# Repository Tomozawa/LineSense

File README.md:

# LineSense
NHK24用ラインセンサ基板。BOMは[こちら](https://docs.google.com/spreadsheets/d/12akROPWRgP_KYzk62EP3h0m6oYP8IBUy/edit?usp=sharing&ouid=100044542046978284478&rtpof=true&sd=true)

## バージョン履歴
### 初期版(2023/9/9)
初期バージョン。
### v1.1(2023/9/9)
センサが5V仕様だったので12Vから5Vに電源を変更。それに伴う回路定数変更。基板にシルク印刷のバージョン表記を追加。

## 概要
地面の色(水性塗料でペイントされている)を判別することができるセンサ。白かそれ以外(青、緑、オレンジ、黄、赤のいずれか)かを判別する。地面の下が白色である確率に応じた振幅の正弦波(10kHz)がSIG_OUTから出力される。出力された信号を包括線検波することで反射率を取得できる。LEDを10kHzで点滅させることで光の反射率をAM変調し、光学フィルタでLEDの波長以外をカットし、Q値の高いLCフィルタで10kHzの信号のみを抽出しているため、比較的地面と離れていても実用に耐えられるよう配慮している。これは、センサの位置を高めにすることでフィールドにある傾斜の影響を極力小さくするためである。

## 基板の作り方(推奨)
部品の温度特性を考慮して、未使用時でも3カ月に1回は校正を行うこと。また、実運用時には機械的な振動で半固定抵抗がずれるため、機体を起動させる際に攻勢を行うこと。

### 1. LED点灯回路を組む
Sheet 2/2 の部品、J1(EPコネクタ)、C7(電解コンデンサ)を取り付け、LEDが点灯することを確認する。また、TP1(テストポイント)から9~12kHzの矩形波が観測されるか確認する。

### 2. 受光回路を組む
Q1, R1, R10, C5を取り付け、白い紙に反射させたLED光に反応することを確認する(10kHz付近の波が確認できるはず)。出力波形はTP2(生信号)またはTP3(カップリング済み信号)で確認できる。信号が弱い場合はR10を時計回りに回すことでゲインを上げる。

### 3. プリアンプ/フィルタ/アンプを組む
残りの部品を取り付け、白い紙に反射させたLED光に反応することを確認する。出力波形はTP5またはコネクタから取ってくる。信号が弱い場合はR5を時計回りに回すことでプリアンプのゲインを上げる。

### 4. 光学フィルタをつける
光センサ(Q1)を20mm平方の青いセロハンで覆う。

### 5. 校正を行う
以下のセクションで説明のある方法で校正を行う。

## 校正の仕方
### LEDの点滅周波数の校正
TP1にオシロスコープのプローブを当て、R16を調整しながら10kHzの矩形波が出力されるようにする。R16を時計回りに回すと周波数が上がり、反時計回りに回すと周波数が下がる。

### 受光回路のゲインの校正
周囲を出来るだけ暗くし、センサを白い紙に水平に設置する。この時の紙との距離は、機体にセンサを搭載した時の高さに合わせる。R10を調整しながらTP3から100mVpp(0.1Vpp)の10kHzの矩形波が出力されるようにする。R10を時計回りに回すと波形が大きくなり、反時計回りに回すと波形が小さくなる。

### プリアンプのゲインの校正
受光回路のゲイン校正と同様の条件に加え、SIG_OUTに36Ωの負荷抵抗を接続した状態で、R5を調整しながらTP5で出てくる信号が歪まないギリギリまでゲインを上げる。TP5からは10kHz正弦波**のみ**が出力されるので、その頂点の部分(約3.0V~3.3V程度)が歪まない(つぶれない)限界までR5を時計回りに回す。

## 課題
### センサと地面の距離による影響が大きい
センサの出力が距離によって大きく変わるため、色の判断のためにはさまざまな波長の光の反射率を取得する必要がある。現状では青色(450nm)の反射率を見ているため、距離の変動による反射率の変化が検出できない

### プリアンプのカップリングコンデンサが機能しない
カップリングコンデンサの後ろを1MΩの抵抗でプルダウンすることでカップリングコンデンサに電流が流れ、カップリングの役割を果たす

### LEDが暗い
Q6のコレクタエミッタ管電圧が低く、負帰還がかかる前に電流が頭打ちになっている。R13を2.2kΩに下げることで90mA程度流れるようになる

### カップリングされているはずなのにプリアンプ出力にDC成分が乗る
原因は分からなかった。出力部分のRCローパスフィルタに原因があるかも。

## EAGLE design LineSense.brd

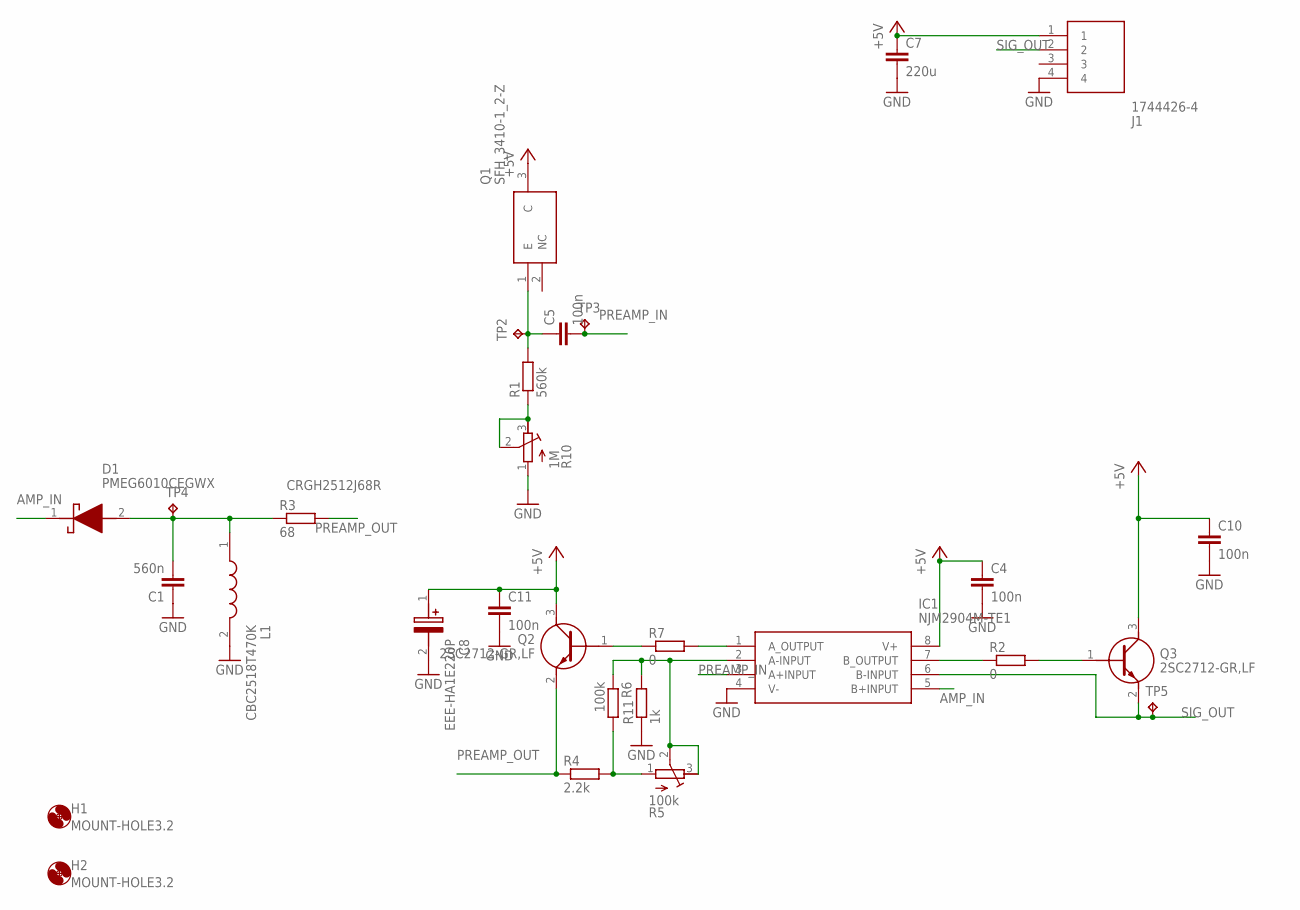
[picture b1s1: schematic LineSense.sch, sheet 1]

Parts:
C1: 560n; C0603
C4, C5, C10, C11: 100n; C0603
C7: 220u; C025-025X050
C8: EEE-HA1E220P; EEE1AA101SP
D1: PMEG6010CEGWX
H1, H2: MOUNT-HOLE3.2; 3,2
IC1: NJM2904M-TE1; SOP65P400X100-8N
J1: 1744426-4; 17444264
L1: CBC2518T470K; INDC2518X200N
Q1: SFH_3410-1_2-Z; SFH341012Z
Q2, Q3: 2SC2712-GR,LF; SSM3J334RLF
R1: 560k; R0603
R2, R7: 0; R0603
R3: 68; R2512
R4: 2.2k; R0603
R5: 100k; RTRIM3339P
R6: 100k; R0603
R10: 1M; RTRIM3339P
R11: 1k; R0603
TP2, TP3, TP4, TP5: TPB1,27; B1,27

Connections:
+5V: C4.1, C7.1, C8.1 (+), C10.1, C11.1, IC1.8 (V+), J1.1, Q1.3 (C), Q2.3 (C), Q3.3 (C); also elsewhere on the board
AMP_IN: D1.1 (K), IC1.5 (B+INPUT)
GND: C1.1, C4.2, C7.2, C8.2 (-), C10.2, C11.2, IC1.4 (V-), J1.4, L1.2, R10.1 (A), R11.1; also elsewhere on the board
unnamed: R1.1, R10.2 (S), R10.3 (E)
unnamed: IC1.1 (A_OUTPUT), R7.2
unnamed: Q2.1 (B), R7.1
unnamed: C5.1, Q1.1 (E), R1.2, TP2.TP
unnamed: R4.2, R5.1 (A), R6.2
unnamed: IC1.2 (A-INPUT), R5.2 (S), R5.3 (E), R6.1, R11.2
unnamed: IC1.7 (B_OUTPUT), R2.1
unnamed: Q3.1 (B), R2.2
unnamed: C1.2, D1.2 (A), L1.1, R3.1, TP4.TP
PREAMP_IN: C5.2, IC1.3 (A+INPUT), TP3.TP
PREAMP_OUT: Q2.2 (E), R3.2, R4.1
SIG_OUT: IC1.6 (B-INPUT), J1.2, Q3.2 (E), TP5.TP

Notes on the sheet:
CRGH2512J68R

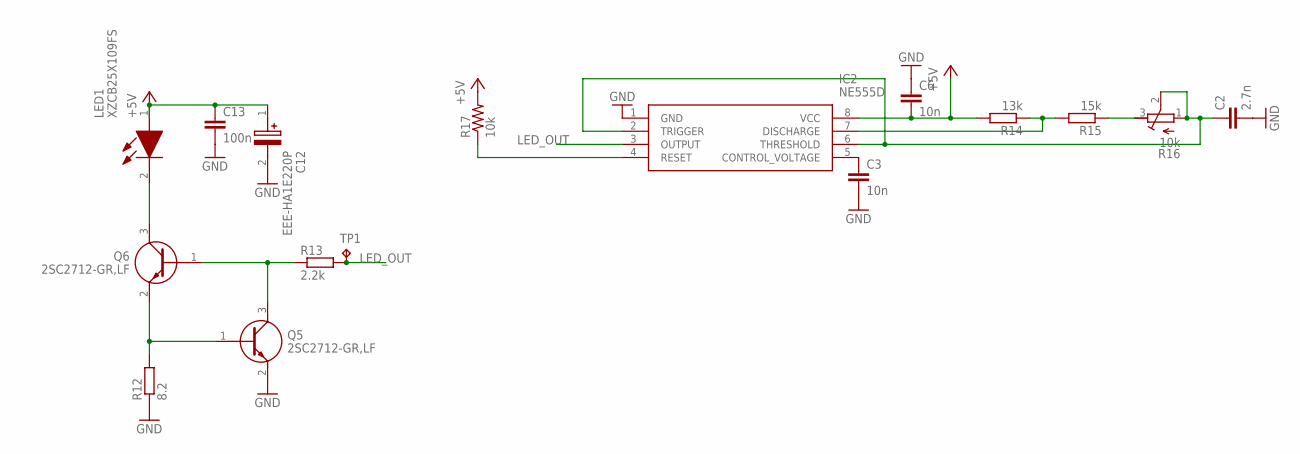
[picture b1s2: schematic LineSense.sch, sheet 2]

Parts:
C2: 2.7n; C0603
C3, C6: 10n; C0603
C12: EEE-HA1E220P; EEE1AA101SP
C13: 100n; C0603
IC2: NE555D; SOIC127P600X200-8N
LED1: XZCB25X109FS
Q5, Q6: 2SC2712-GR,LF; SSM3J334RLF
R12: 8.2; R0603
R13: 2.2k; R0603
R14: 13k; R0603
R15: 15k; R0603
R16: 10k; RTRIM3339P
R17: 10k; R0603
TP1: TPB1,27; B1,27

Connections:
+5V: C6.2, C12.1 (+), C13.1, IC2.8 (VCC), LED1.1 (A), R14.2, R17.2; also elsewhere on the board
GND: C2.2, C3.2, C6.1, C12.2 (-), C13.2, IC2.1 (GND), Q5.2 (E), R12.1; also elsewhere on the board
LED_OUT: IC2.3 (OUTPUT), R13.2, TP1.TP
unnamed: LED1.2 (K), Q6.3 (C)
unnamed: Q5.1 (B), Q6.2 (E), R12.2
unnamed: Q5.3 (C), Q6.1 (B), R13.1
unnamed: C3.1, IC2.5 (CONTROL_VOLTAGE)
unnamed: IC2.4 (RESET), R17.1
unnamed: C2.1, IC2.2 (TRIGGER), IC2.6 (THRESHOLD), R16.1 (A), R16.2 (S)
unnamed: IC2.7 (DISCHARGE), R14.1, R15.2
unnamed: R15.1, R16.3 (E)

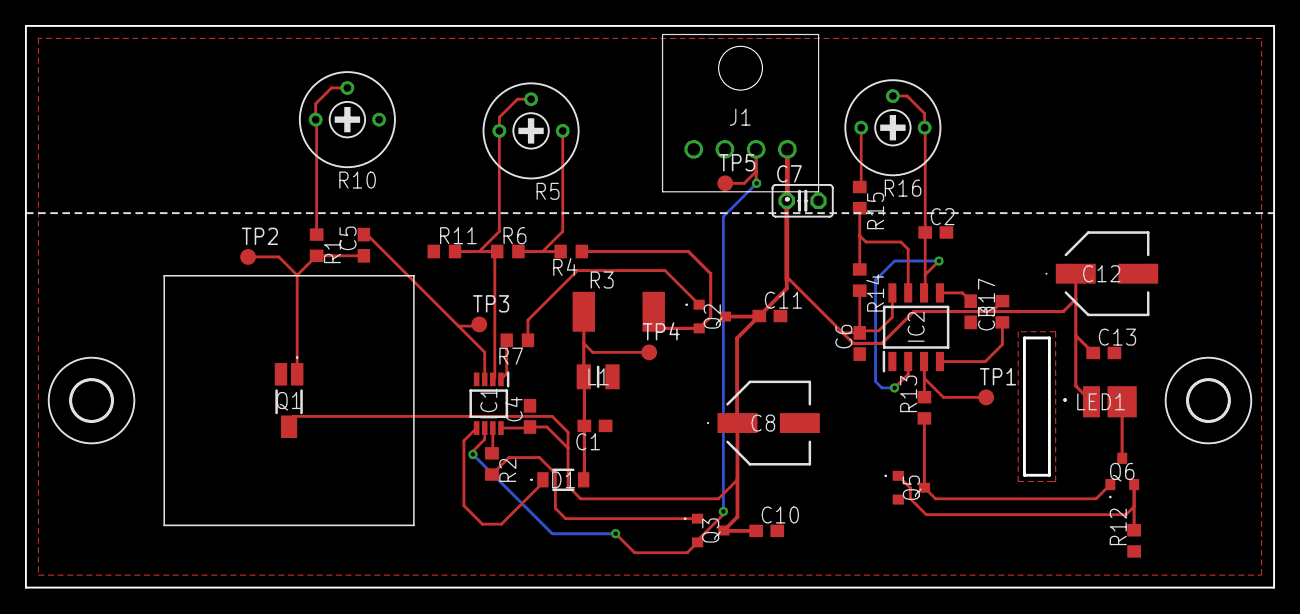
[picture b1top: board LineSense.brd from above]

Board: 2 copper layers, 99.9 x 44.9 mm, 45 parts (0 on the bottom side), 24 nets.

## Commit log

2023-09-09 BOM info
2023-09-09 v1.2
2023-09-16 Revert "BOM info"
    This reverts commit b7451d02ac79e986c6a60497e87a7443eaa3fbfb.
2023-09-16 before revert
2023-09-16 Revert "before revert"
    This reverts commit e8f8bca6d98889abda275bddc4be13dac5328736.
2023-09-16 Revert "Revert "before revert""
    This reverts commit 7b5b295e3937b90656ff80f37ae6d33e2d9af6bb.
2023-09-16 Revert "Revert "Revert "before revert"""
    This reverts commit 50fdca305e50505982d5631dc0ec61948265d2f3.
2023-09-16 Revert "Revert "Revert "Revert "before revert""""
    This reverts commit 6fd7e8f189b9fc5cd2685d5a5b0e8bcca15d70bf.
2023-09-16 Revert "Revert "BOM info""
    This reverts commit 3cd070827710dd9a6509c16180cd1ad1550c4722.
2023-09-16 Revert "Update README"
    This reverts commit 9517380c4df702eee66446d714f26b74ab81f7a8.
2023-09-16 Revert "Update README"
    This reverts commit 3503a3691537a7a45706d27a9126bd11c90a7538.
2023-09-16 Revert "Update README"
    This reverts commit dc8250fc835837e6ad62376d3f5ed4d1ab16a480.
2023-09-16 Revert "Update README"
    This reverts commit 9ea362463da6671fc085362a8b1ee711a42e3dd3.
2023-09-16 Revert "v1.2"
    This reverts commit 20100e136a2bdf049fa62e188f43b768e8603774.
2023-09-16 Revert"Update README"
2023-09-16 Revert "Revert"Update README""
    This reverts commit 0f7fe967b72114c67d75a17a1a4153d7b0fd92ee.
2023-09-16 Revert "Revert "BOM info""
    This reverts commit b29b347e91c00aeff9c3f0b2e26896e121cc4927.
2023-09-16 "v1.2"
    This reverts commit e496e1b4c8a1751f90fa83cfac83a30d936792d4.
2023-09-24 The First ver2.x
2023-09-24 Update load resistance of reciever
2023-09-30 modify
